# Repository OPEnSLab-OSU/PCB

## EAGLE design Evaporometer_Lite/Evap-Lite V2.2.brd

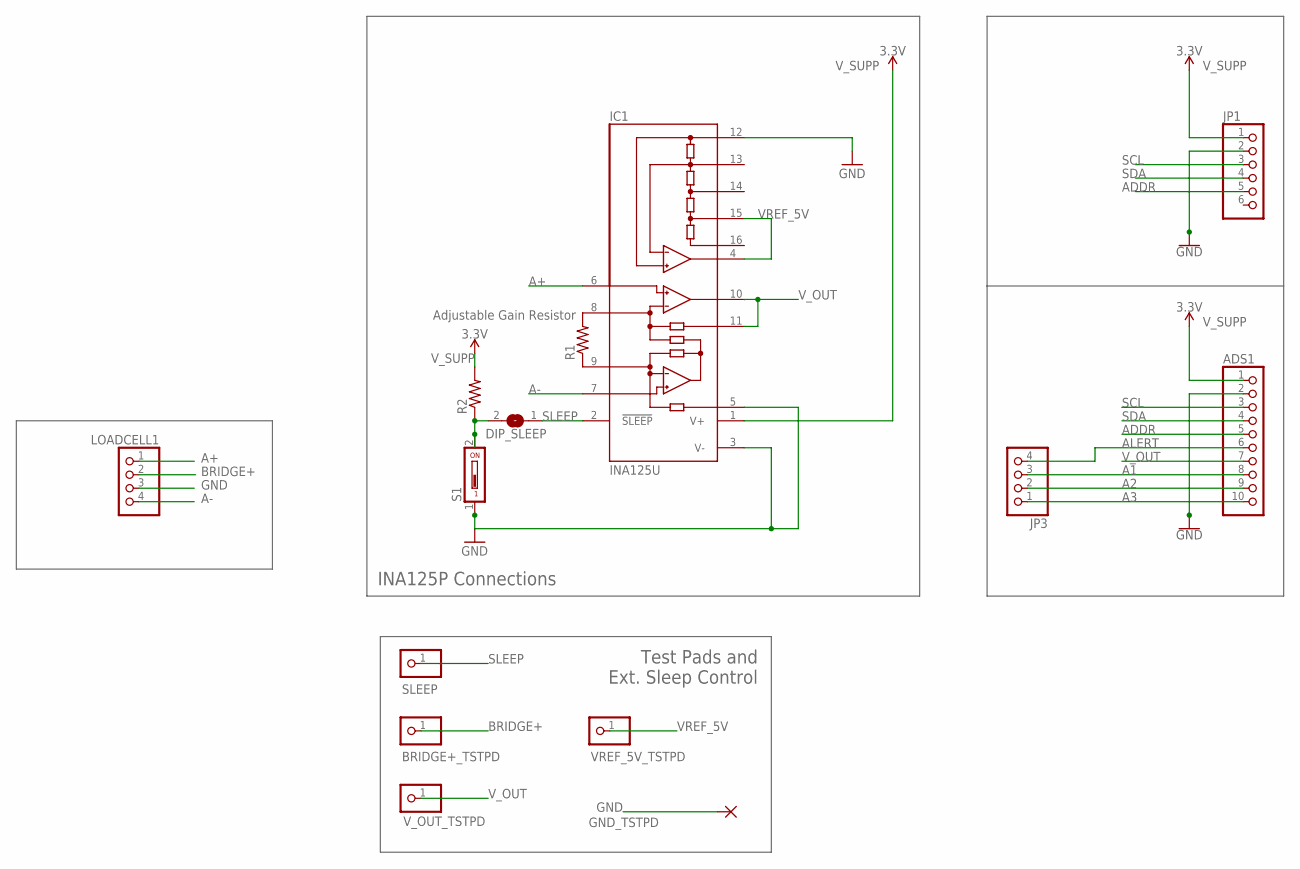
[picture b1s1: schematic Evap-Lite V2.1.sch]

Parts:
ADS1: PINHD-1X10; 1X10
BRIDGE+_TSTPD: PINHD-1X1; 1X01
DIP_SLEEP: SJ
GND_TSTPD: WIREPADSMD2,54-5,08; SMD2,54-5,08
IC1: INA125U; SO16-1
JP1: PINHD-1X6; 1X06
JP3: PINHD-1X4; 1X04
LOADCELL1: PINHD-1X4; 1X04
R1: R-US_R0603; R0603
R2: R-US_R1206; R1206
S1: DS01; DS-01
SLEEP: PINHD-1X1; 1X01
VREF_5V_TSTPD: PINHD-1X1; 1X01
V_OUT_TSTPD: PINHD-1X1; 1X01

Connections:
A1: ADS1.8, JP3.3
A2: ADS1.9, JP3.2
A3: ADS1.10, JP3.1
A+: IC1.6 (+IN), LOADCELL1.1
A-: IC1.7 (-IN), LOADCELL1.4
ADDR: ADS1.5, JP1.5
ALERT: ADS1.6, JP3.4
BRIDGE+: BRIDGE+_TSTPD.1, LOADCELL1.2
GND: ADS1.2, GND_TSTPD.1, IC1.3 (V-), IC1.5 (REF), IC1.12 (REFCOM), JP1.2, LOADCELL1.3, S1.1
unnamed: DIP_SLEEP.2, R2.1, S1.2
RG+: IC1.9 (RG), R1.1
RG-: IC1.8 (RG), R1.2
SCL: ADS1.3, JP1.3
SDA: ADS1.4, JP1.4
SLEEP: DIP_SLEEP.1, IC1.2 (!SLEEP), SLEEP.1
VREF_5V: IC1.4 (REFOUT), IC1.15 (REF5), VREF_5V_TSTPD.1
V_OUT: ADS1.7, IC1.10 (OUT), IC1.11 (SENSE), V_OUT_TSTPD.1
V_SUPP: ADS1.1, IC1.1 (V+), JP1.1, R2.2

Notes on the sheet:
Adjustable Gain Resistor
INA125P Connections
Test Pads and Ext. Sleep Control

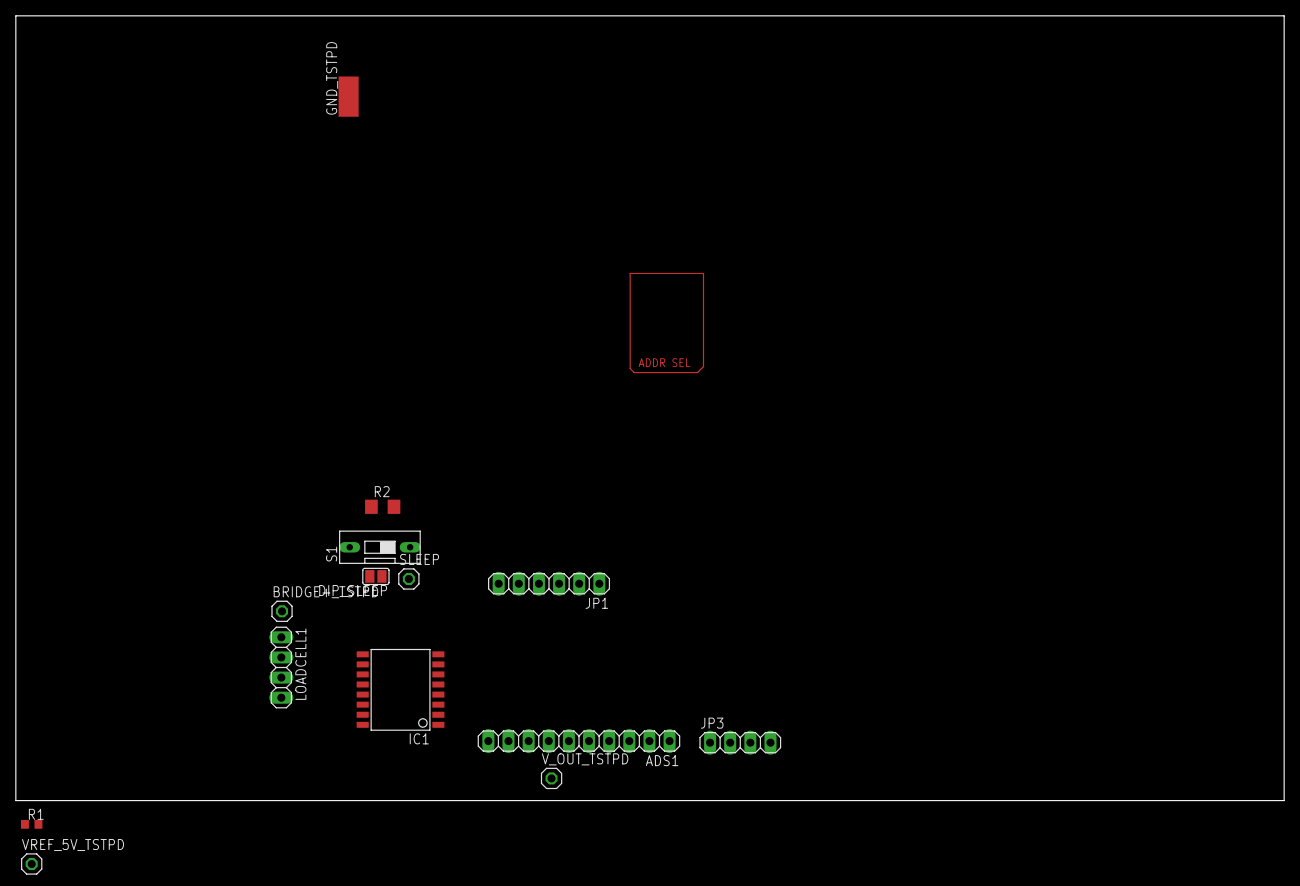
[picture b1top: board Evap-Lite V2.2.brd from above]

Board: 2 copper layers, 160.0 x 99.0 mm, 14 parts (0 on the bottom side), 18 nets.

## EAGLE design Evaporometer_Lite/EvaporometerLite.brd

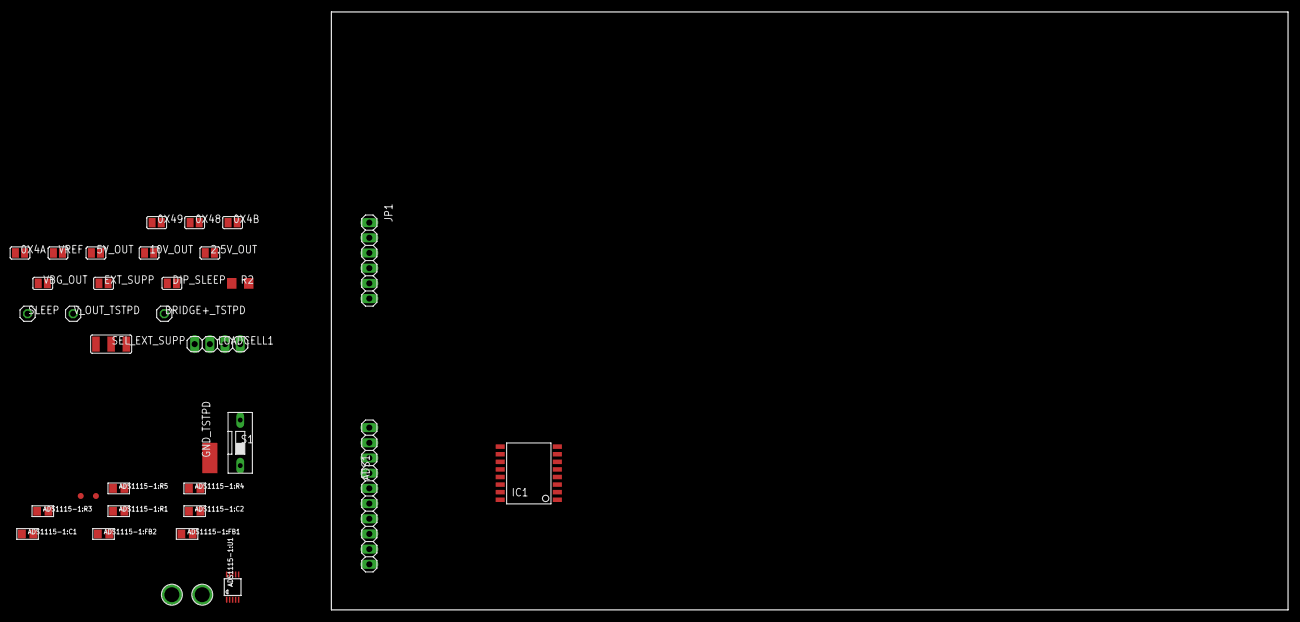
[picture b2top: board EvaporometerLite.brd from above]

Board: 2 copper layers, 160.0 x 100.0 mm, 35 parts (0 on the bottom side), 24 nets, no tracks yet.

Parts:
0X4A, 0X4B, 0X48, 0X49, 2.5V_OUT, 5V_OUT, 10V_OUT: SJ
ADS1: 1X10
ADS1115-1:C1, ADS1115-1:C2: 1µF; 0805
ADS1115-1:FB1, ADS1115-1:FB2: MMZ2012Y152B; 0805
ADS1115-1:FID1, ADS1115-1:FID2: FIDUCIAL""; FIDUCIAL_1MM
ADS1115-1:R1, ADS1115-1:R3, ADS1115-1:R4, ADS1115-1:R5: 10K; 0805
ADS1115-1:U1: ADS1115IDGST; MSOP10
ADS1115-1:U$13, ADS1115-1:U$14: MOUNTINGHOLE2.5; MOUNTINGHOLE_2.5_PLATED
BRIDGE+_TSTPD: 1X01
DIP_SLEEP: SJ
EXT_SUPP: SJ
GND_TSTPD: WIREPADSMD2,54-5,08; SMD2,54-5,08
IC1: INA125U; SO16-1
JP1: 1X06
LOADCELL1: 1X04
R2: R1206
S1: DS-01
SEL_EXT_SUPP: SJ_2W
SLEEP: 1X01
VBG_OUT: SJ
VREF: SJ
V_OUT_TSTPD: 1X01

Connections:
A1: ADS1.8, ADS1115-1:U1.5
A2: ADS1.9, ADS1115-1:U1.6
A3: ADS1.10, ADS1115-1:U1.7
A+: IC1.6, LOADCELL1.1
A-: IC1.7, LOADCELL1.4
ADDR: 0X4A.2, 0X4B.2, 0X48.2, 0X49.2, ADS1.5, ADS1115-1:R4.1, ADS1115-1:U1.1, JP1.5
ADS1115-1:GND: ADS1115-1:C1.1, ADS1115-1:FB2.2, ADS1115-1:R4.2, ADS1115-1:U1.3
ADS1115-1:VDD: ADS1115-1:C1.2, ADS1115-1:FB1.2, ADS1115-1:R1.1, ADS1115-1:R3.1, ADS1115-1:R5.1, ADS1115-1:U1.8
ALERT: ADS1.6, ADS1115-1:R5.2, ADS1115-1:U1.2
BRIDGE+: BRIDGE+_TSTPD.1, EXT_SUPP.1, LOADCELL1.2, VREF.1
GND: 0X48.1, ADS1.2, ADS1115-1:C2.2, ADS1115-1:FB2.1, GND_TSTPD.1, IC1.3, IC1.5, IC1.12, JP1.2, LOADCELL1.3, S1.1
unnamed: JP1.6, SEL_EXT_SUPP.3
unnamed: DIP_SLEEP.2, R2.1, S1.2
SCL: 0X4B.1, ADS1.3, ADS1115-1:R1.2, ADS1115-1:U1.10, JP1.3
SDA: 0X4A.1, ADS1.4, ADS1115-1:R3.2, ADS1115-1:U1.9, JP1.4
SLEEP: DIP_SLEEP.1, IC1.2, SLEEP.1
VREF_2.5V: 2.5V_OUT.2, IC1.14
VREF_5V: 5V_OUT.2, IC1.15
VREF_10V: 10V_OUT.2, IC1.16
VREF_BG: IC1.13, VBG_OUT.2
VREF_EXT: EXT_SUPP.2, SEL_EXT_SUPP.2
VREF_OUT: 2.5V_OUT.1, 5V_OUT.1, 10V_OUT.1, IC1.4, VBG_OUT.1, VREF.2
V_OUT: ADS1.7, ADS1115-1:U1.4, IC1.10, IC1.11, V_OUT_TSTPD.1
V_SUPP: 0X49.1, ADS1.1, ADS1115-1:C2.1, ADS1115-1:FB1.1, IC1.1, JP1.1, R2.2, SEL_EXT_SUPP.1

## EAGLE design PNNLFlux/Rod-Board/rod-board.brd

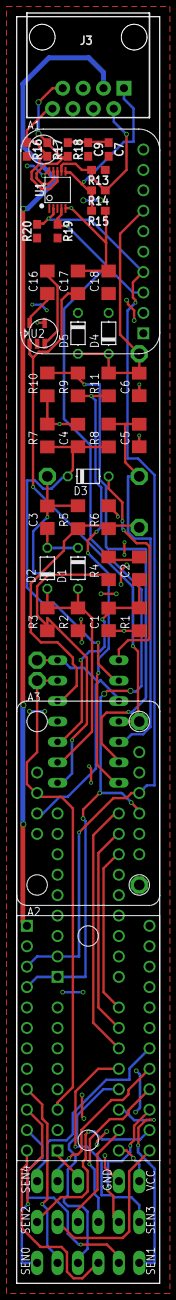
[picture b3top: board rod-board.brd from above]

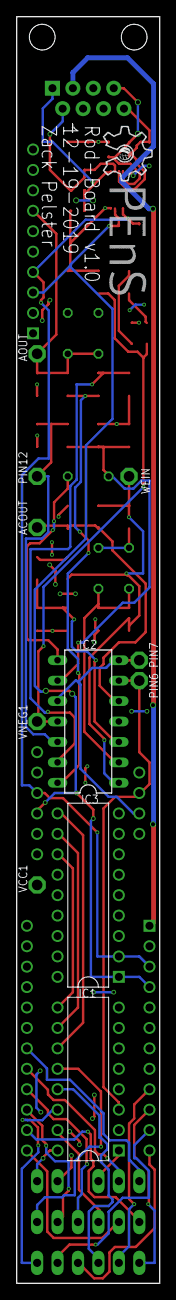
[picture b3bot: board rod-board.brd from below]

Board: 2 copper layers, 17.8 x 157.5 mm, 59 parts (12 on the bottom side), 44 nets.

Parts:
A1: ADS1115
A2: TCA9548A
A3: DS3502
ACOUT: PTR1PAD1-13; P1-13
AOUT: PTR1PAD1-13; P1-13
C1, C2, C3: 100nF; C1206
C4, C5, C6, C16, C17, C18: 1uF; C1206
C7: 0.1uF; 0603
C9: 1.0uF; 0603
D1, D2, D3, D4, D5: 1N4001; D-5
IC1: CD4051BE
IC2: TL074P; DIL14
IC3: MCP23008
J3: RJ45; RJ45-8
JP1: SENSOR0; 1X03
JP2: SENSOR1; 1X03
JP3: SENSOR2; 1X03
JP4: SENSOR3; 1X03
JP5: SENSOR4; 1X03
JP6: POWER; 1X02
PIN6, PIN7, PIN12: PTR1PAD1-13; P1-13
R1, R4, R6: 1K; R1206
R2, R7, R9: 10K; R1206
R3: 22K; R1206
R5: 2K; R1206
R8, R11: 4.7K; R1206
R10: 5K; R1206
R13, R15, R16, R18: 390; 0603
R14, R17: 100; 0603
R19, R20: 4.7k; 0603
U1: PCA9615; TSSOP10
U2: TPS60400DBVR; SOT95P280X145-5N
U$1: OPENS-LOGO
VCC1: PTR1PAD1-13; P1-13
VNEG1: PTR1PAD1-13; P1-13
WEIN: PTR1PAD1-13; P1-13

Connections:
3V_I2C: A2.VIN, J3.3
A: IC1.A, IC3.GP0
AIN: A3.RH, IC1.COM, IC2.6, PIN6.TP
AOUT: A1.A0, AOUT.TP, C6.2, D4.C, D5.A, R11.2
B: IC1.B, IC3.GP1
C: IC1.C, IC3.GP2
DSCL+: J3.2, R13.1, R14.2, U1.7
DSCL-: J3.1, R14.1, R15.2, U1.6
DSDA+: J3.8, R16.1, R17.2, U1.8
DSDA-: J3.7, R17.1, R18.2, U1.9
EC0: IC1.0, JP1.3
EC1: IC1.1, JP2.3
EC2: IC1.2, JP3.3
EC3: IC1.3, JP4.3
EC4: IC1.4, JP5.3
GND: A1.GND, A2.GND, A3.GND, A3.RL, C1.2, C4.1, C5.1, C6.1, C7.2, C9.2, C17.1, C18.1, D4.A, IC1.VEE, IC3.VSS, J3.5, JP6.1, R1.1, R2.2, R6.1, R7.1, R10.2, R15.1, R18.1, U1.5, U2.4
unnamed: C1.1, C2.1, IC2.3, R1.2
unnamed: C2.2, R4.2
unnamed: C3.2, IC2.1, R3.1, R4.1, R5.2, WEIN.TP
unnamed: D1.A, D2.C, IC2.2, R2.1, R3.2
unnamed: ACOUT.TP, IC2.5, R5.1, R6.2
unnamed: C3.1, D1.C, D2.A
unnamed: C4.2, D3.C, IC2.9, R7.2, R8.2
unnamed: D3.A, IC2.8
unnamed: C5.2, IC2.12, PIN12.TP, R8.1
unnamed: IC2.13, R9.2, R10.1
unnamed: IC2.14, R9.1, R11.1
unnamed: C16.2, U2.5
unnamed: C16.1, U2.3
POT: A3.RW, IC2.7, IC2.10, PIN7.TP
SC0: A2.SC0, JP1.1
SC1: A2.SC1, JP2.1
SC2: A2.SC2, JP3.1
SC3: A2.SC3, JP4.1
SC4: A2.SC4, JP5.1
SCL: A1.SCL, A2.SCL, A3.SCL, IC3.SCL, R19.1, U1.4
SD0: A2.SD0, JP1.2
SD1: A2.SD1, JP2.2
SD2: A2.SD2, JP3.2
SD3: A2.SD3, JP4.2
SD4: A2.SD4, JP5.2
SDA: A1.SDA, A2.SDA, A3.SDA, IC3.SDA, R20.1, U1.2
VCC: A1.VDD, A3.VCC, C7.1, C9.1, C18.2, D5.C, IC1.VDD, IC2.4, IC3.VDD, J3.4, JP6.2, R13.2, R16.2, R19.2, R20.2, U1.1, U1.10, U2.2, VCC1.TP
VNEG: C17.2, IC2.11, U2.1, VNEG1.TP

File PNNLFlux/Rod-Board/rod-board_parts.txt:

Partlist

Exported from rod-board.brd at 12/20/19 8:15 AM

EAGLE Version 9.5.1 Copyright (c) 1988-2019 Autodesk, Inc.

Assembly variant: 

Part     Value          Package          Library             Position (inch)       Orientation

A1       ADS1115        ADS1115          PNNL_Probe          (0.7 3.3)             R90
A2       TCA9548A       TCA9548A         PNNL_Probe          (0 4.45)              R0
A3       DS3502         DS3502           PNNL_Probe          (0.7 2.25)            R90
ACOUT    PTR1PAD1-13    P1-13            testpad             (0.6 1.2)             R0
AOUT     PTR1PAD1-13    P1-13            testpad             (0.6 2.1)             R0
C1       100nF          C1206            rcl                 (0.45 0.75)           R270
C2       100nF          C1206            rcl                 (0.6 1)               R90
C3       100nF          C1206            rcl                 (0.15 1.25)           R90
C4       1uF            C1206            rcl                 (0.3 1.65)            R270
C5       1uF            C1206            rcl                 (0.6 1.65)            R90
C6       1uF            C1206            rcl                 (0.6 1.9)             R90
C7       0.1uF          0603             SparkFun-Capacitors (0.25 5.6)            R270
C9       1.0uF          0603             SparkFun-Capacitors (0.45 5.6)            R270
C16      1uF            C1206            rcl                 (0.15 2.4)            R270
C17      1uF            C1206            rcl                 (0.3 2.4)             R270
C18      1uF            C1206            rcl                 (0.45 2.4)            R270
D1       1N4001         D-5              diode               (0.3 1)               R270
D2       1N4001         D-5              diode               (0.15 1)              R90
D3       1N4001         D-5              diode               (0.35 1.45)           R0
D4       1N4001         D-5              diode               (0.45 2.15)           R90
D5       1N4001         D-5              diode               (0.3 2.15)            R270
IC1      CD4051BE       CD4051BE         PNNL_Probe          (0.15 3.45)           MR90
IC2      TL074P         DIL14            linear              (0.35 3)              MR90
IC3      MCP23008       MCP23008         PNNL_Probe          (0.1 4.25)            MR90
J3       RJ45           RJ45-8           SparkFun-Connectors (0.35 6.1)            R180
JP1                     1X03             pinhead             (0.2 0.1)             R0
JP2                     1X03             pinhead             (0.5 0.1)             R0
JP3                     1X03             pinhead             (0.2 0.3)             R0
JP4                     1X03             pinhead             (0.5 0.3)             R0
JP5                     1X03             pinhead             (0.2 0.5)             R0
JP6                     1X02             pinhead             (0.55 0.5)            R0
PIN6     PTR1PAD1-13    P1-13            testpad             (0.6 3.2)             MR0
PIN7     PTR1PAD1-13    P1-13            testpad             (0.1 3.1)             MR0
PIN12    PTR1PAD1-13    P1-13            testpad             (0.6 1.45)            R0
R1       1K             R1206            rcl                 (0.6 0.75)            R90
R2       10K            R1206            rcl                 (0.3 0.75)            R270
R3       22K            R1206            rcl                 (0.15 0.75)           R90
R4       1K             R1206            rcl                 (0.45 1)              R90
R5       2K             R1206            rcl                 (0.3 1.25)            R90
R6       1K             R1206            rcl                 (0.45 1.25)           R270
R7       10K            R1206            rcl                 (0.15 1.65)           R270
R8       4.7K           R1206            rcl                 (0.45 1.65)           R270
R9       10K            R1206            rcl                 (0.3 1.9)             R90
R10      5K             R1206            rcl                 (0.15 1.9)            R270
R11      4.7K           R1206            rcl                 (0.45 1.9)            R90
R13      390            0603             SparkFun-Resistors  (0.55 5.6)            R90
R14      100            0603             SparkFun-Resistors  (0.55 5.45)           R90
R15      390            0603             SparkFun-Resistors  (0.55 5.3)            R90
R16      390            0603             SparkFun-Resistors  (0.15 5.6)            R90
R17      100            0603             SparkFun-Resistors  (0.15 5.45)           R90
R18      390            0603             SparkFun-Resistors  (0.15 5.3)            R90
R19      4.7k           0603             SparkFun-Resistors  (0.25 5.2)            R0
R20      4.7k           0603             SparkFun-Resistors  (0.45 5.2)            R180
U1       PCA9615        TSSOP10          SparkFun-IC-Comms   (0.35 5.4)            R0
U2       TPS60400DBVR   SOT95P280X145-5N TPS60400DBVR        (0.1 2.15)            R90
VCC1     PTR1PAD1-13    P1-13            testpad             (0.6 2.35)            MR270
VNEG1    PTR1PAD1-13    P1-13            testpad             (0.1 3)               MR0
WEIN     PTR1PAD1-13    P1-13            testpad             (0.15 1.45)           R0

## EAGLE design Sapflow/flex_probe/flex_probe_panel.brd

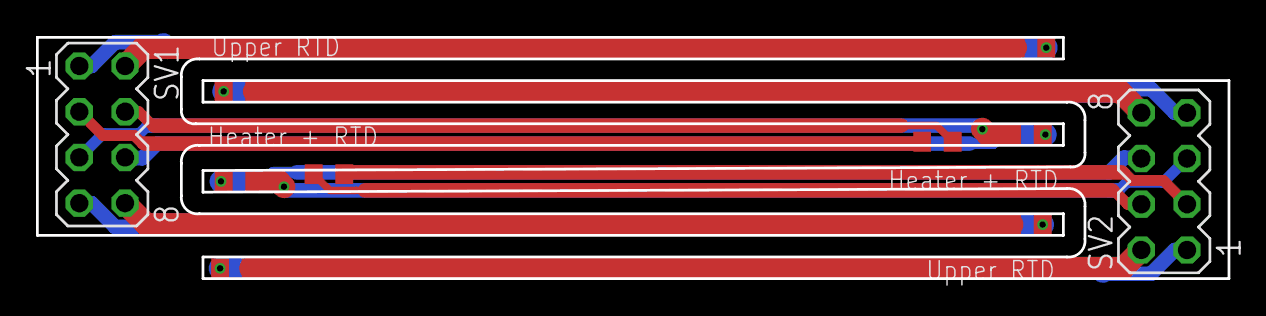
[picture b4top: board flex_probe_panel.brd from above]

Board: 2 copper layers, 66.2 x 13.4 mm, 10 parts (0 on the bottom side), 16 nets.

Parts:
R1, R2, R4, R5, R6, R8: RTD; R0603
R3, R7: 100; R0603
SV1, SV2: MA04-2

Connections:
unnamed: R1.2, SV1.2
unnamed: R1.1, SV1.1
unnamed: R2.2, SV1.4
unnamed: R2.1, SV1.3
unnamed: R6.2, SV2.4
unnamed: R6.1, SV2.3
unnamed: R4.1, SV1.7
unnamed: R3.2, SV1.6
unnamed: R3.1, SV1.5
unnamed: R8.1, SV2.7
unnamed: R4.2, SV1.8
unnamed: R7.2, SV2.6
unnamed: R7.1, SV2.5
unnamed: R5.2, SV2.2
unnamed: R5.1, SV2.1
unnamed: R8.2, SV2.8

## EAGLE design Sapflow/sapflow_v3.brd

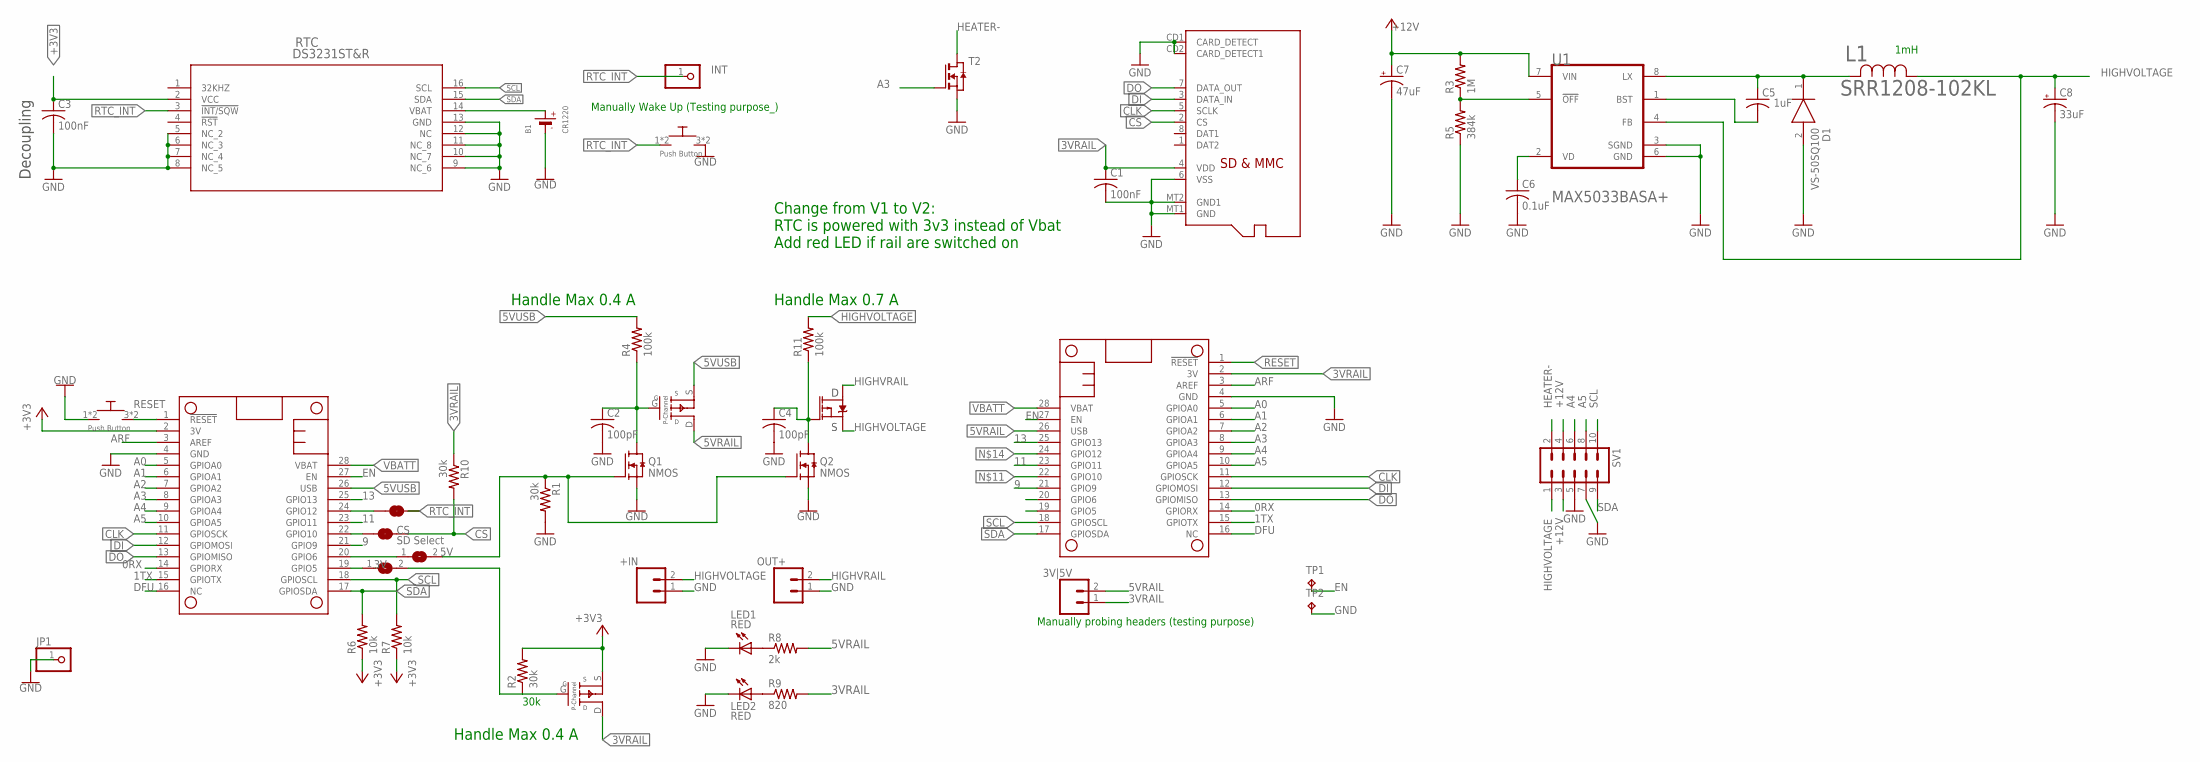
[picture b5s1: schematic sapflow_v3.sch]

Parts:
3V, 5V: SJ
3V|5V: CONN_021X02_NO_SILK; 1X02_NO_SILK
+IN: HIGHV-IN; 1X02_NO_SILK
B1: CR1220
C1, C3: 100nF; C1206
C2, C4: 100pF; C0805
C5: 1uF; C0603
C6: 0.1uF; C0603
C7: 47uF; D/7343-31R
C8: 33uF; D/7343-31R
CS: SD Select; SMT-JUMPER_2_NC_TRACE_SILK
D1: VS-50SQ100; DIOAD1405W86L465D235
INT: PINHD-1X1CB; 1X01-CLEANBIG
JP1: PINHD-1X1CB; 1X01-CLEANBIG
L1: SRR1208-102KL; IND_BOURNS_SRR1208
LED1, LED2: RED; CHIPLED_0805
MICROSD: MICROSD
MS1, MS2: FEATHERWING
OUT+: HIGHV-OUT; 1X02_NO_SILK
PMOS1, PMOS2: SSM3J3228R; SOT-23-3
PMOS3: P-MOSFET; SOT23-6
Q1, Q2: NMOS; SOT23-S
R1, R2, R10: 30k; RES_1206
R3: 1M; R0603
R4, R11: 100k; RES_1206
R5: 384k; R0603
R6, R7: 10k; RES_1206
R8: 2k; RES_1206
R9: 820; RES_1206
RTC: DS3231ST&R; 21-0042B_16
RTC_INT: JUMPER-SMT_2_NC_TRACE_SILK; SMT-JUMPER_2_NC_TRACE_SILK
SV1: MA05-2
T2: NMOSSOT223; SOT223
TP1, TP2: TPTP16R; TP16R
U1: MAXIM_MAX5033BASA+MAXIM_MAX5033BASA+_0_1; MAXIM_MAX5033BASA+_1
U$1, U$2: PUSH_BUTTON; PUSHBUTTON_SMD

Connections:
0RX: MS1.14 (GPIORX), MS2.14 (GPIORX)
1TX: MS1.15 (GPIOTX), MS2.15 (GPIOTX)
3VRAIL: 3V|5V.1, C1.1, MICROSD.4 (VDD), MS1.2 (3V), PMOS2.D, R9.2, R10.1
5VRAIL: 3V|5V.2, MS1.26 (USB), PMOS1.D, R8.2
5VUSB: MS2.26 (USB), PMOS1.S, R4.2
9: MS1.21 (GPIO9), MS2.21 (GPIO9)
11: MS1.23 (GPIO11), MS2.23 (GPIO11)
13: MS1.25 (GPIO13), MS2.25 (GPIO13)
+3V3: C3.1, MS2.2 (3V), PMOS2.S, R2.2, R6.1, R7.1, RTC.2 (VCC)
+12V: C7.+, R3.2, SV1.3, SV1.4, U1.7 (VIN)
A0: MS1.5 (GPIOA0), MS2.5 (GPIOA0)
A1: MS1.6 (GPIOA1), MS2.6 (GPIOA1)
A2: MS1.7 (GPIOA2), MS2.7 (GPIOA2)
A3: MS1.8 (GPIOA3), MS2.8 (GPIOA3), T2.1 (G)
A4: MS1.9 (GPIOA4), MS2.9 (GPIOA4), SV1.6
A5: MS1.10 (GPIOA5), MS2.10 (GPIOA5), SV1.8
ARF: MS1.3 (AREF), MS2.3 (AREF)
CLK: MICROSD.5 (SCLK), MS1.11 (GPIOSCK), MS2.11 (GPIOSCK)
CS: CS.2, MICROSD.2 (CS), R10.2
DFU: MS1.16 (NC), MS2.16 (NC)
DI: MICROSD.3 (DATA_IN), MS1.12 (GPIOMOSI), MS2.12 (GPIOMOSI)
DO: MICROSD.7 (DATA_OUT), MS1.13 (GPIOMISO), MS2.13 (GPIOMISO)
EN: MS1.27 (EN), MS2.27 (EN), TP1.TP
GND: +IN.1, B1.-, C1.2, C2.2, C3.2, C4.2, C6.2, C7.-, C8.-, D1.2 (A), JP1.1, LED1.C, LED2.C, MICROSD.6 (VSS), MICROSD.CD1 (CARD_DETECT), MICROSD.CD2 (CARD_DETECT1), MICROSD.MT1 (GND), MICROSD.MT2 (GND1), MS1.4 (GND), MS2.4 (GND), OUT+.1, Q1.2 (S), Q2.2 (S), R1.2, R5.1, RTC.5 (NC_2), RTC.6 (NC_3), RTC.7 (NC_4), RTC.8 (NC_5), RTC.9 (NC_6), RTC.10 (NC_7), RTC.11 (NC_8), RTC.12 (NC), RTC.13 (GND), SV1.5, SV1.7, T2.3 (S), TP2.TP, U1.3 (SGND), U1.6 (GND), U$1.1, U$1.2, U$2.3, U$2.4
HEATER-: SV1.2, T2.2 (D), T2.4 (D)
HIGHVOLTAGE: +IN.2, C8.+, L1.1, PMOS3.4 (S), R11.2, SV1.1, U1.4 (FB)
HIGHVRAIL: OUT+.2, PMOS3.1 (D), PMOS3.2 (D), PMOS3.5 (D), PMOS3.6 (D)
unnamed: 5V.1, MS2.20 (GPIO6)
unnamed: B1.+$1 (+), RTC.14 (VBAT)
unnamed: 3V.1, MS2.19 (GPIO5)
unnamed: 5V.2, Q1.1 (G), Q2.1 (G), R1.1
unnamed: 3V.2, PMOS2.G, R2.1
unnamed: C6.1, U1.2 (VD)
unnamed: R3.1, R5.2, U1.5 (!OFF!)
unnamed: C2.1, PMOS1.G, Q1.3 (D), R4.1
unnamed: CS.1, MS1.22 (GPIO10), MS2.22 (GPIO10)
unnamed: LED1.A, R8.1
unnamed: LED2.A, R9.1
unnamed: MS1.24 (GPIO12), MS2.24 (GPIO12), RTC_INT.1
unnamed: C4.1, PMOS3.3 (G), Q2.3 (D), R11.1
unnamed: C5.2, U1.1 (BST)
unnamed: C5.1, D1.1 (K), L1.2, U1.8 (LX)
RESET: MS1.1 (!RESET), MS2.1 (!RESET), U$1.3, U$1.4
RTC_INT: INT.1, RTC.3 (!INT/SQW), RTC_INT.2, U$2.1, U$2.2
SCL: MS1.18 (GPIOSCL), MS2.18 (GPIOSCL), R7.2, RTC.16 (SCL), SV1.10
SDA: MS1.17 (GPIOSDA), MS2.17 (GPIOSDA), R6.2, RTC.15 (SDA), SV1.9
VBATT: MS1.28 (VBAT), MS2.28 (VBAT)

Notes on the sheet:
Decoupling
Manually Wake Up (Testing purpose_)
Manually probing headers (testing purpose)
30k
Change from V1 to V2: RTC is powered with 3v3 instead of Vbat Add red LED if rail are switched on
Handle Max 0.7 A
Handle Max 0.4 A
1mH

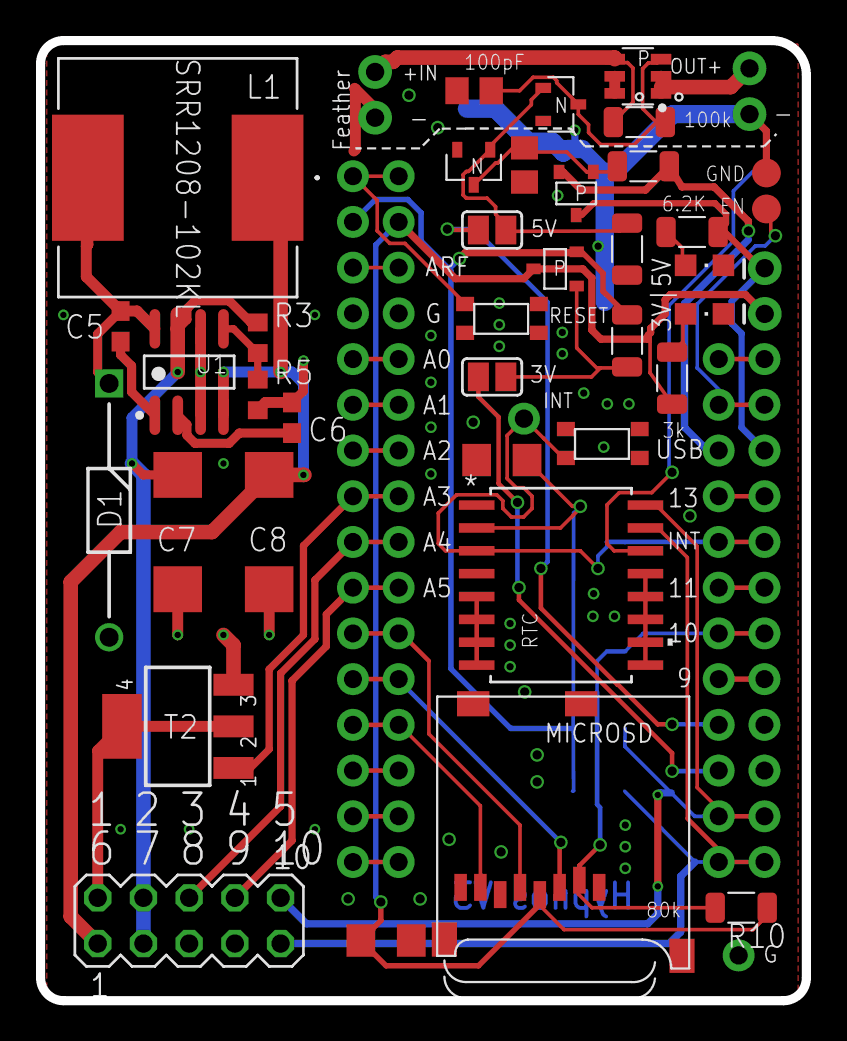
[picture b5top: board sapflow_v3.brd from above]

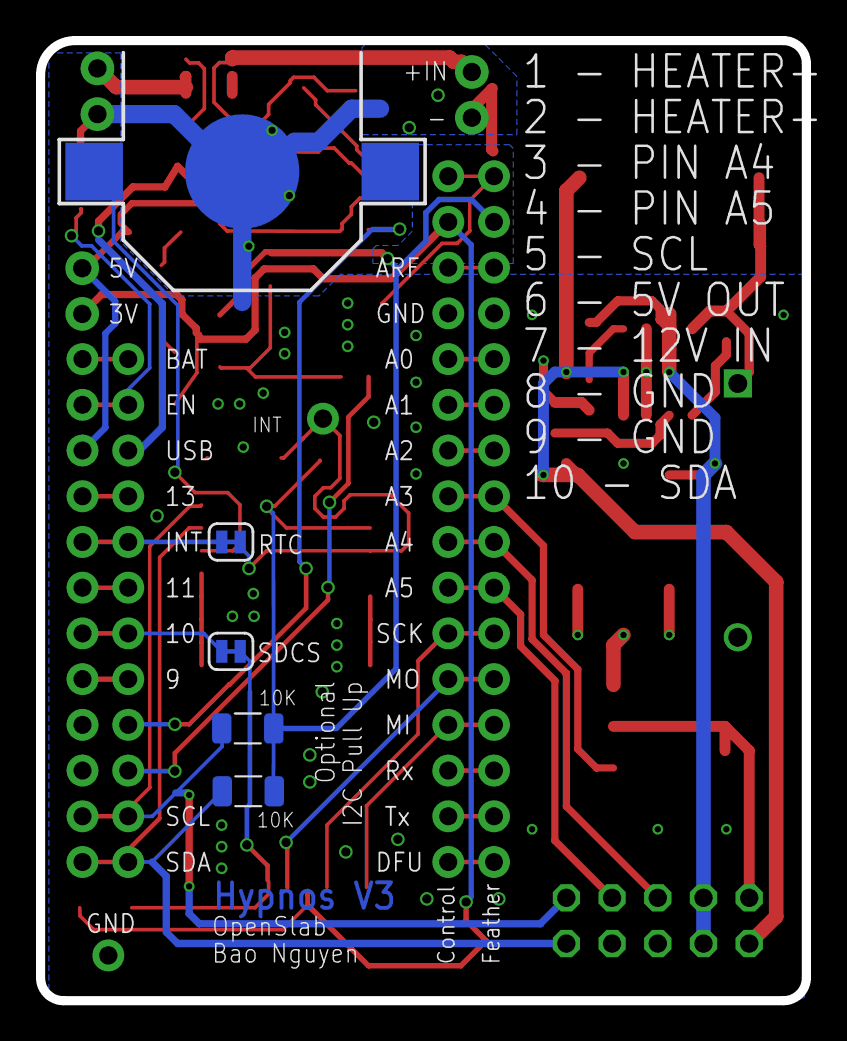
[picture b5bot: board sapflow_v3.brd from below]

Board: 2 copper layers, 42.5 x 53.3 mm, 49 parts (6 on the bottom side), 47 nets.

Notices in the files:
parts and their libraries:
SparkFun-PowerSymbols: Licensing: Creative Commons ShareAlike 4.0 International - https://creativecommons.org/licenses/by-sa/4.0
microbuilder: This work is placed in the public domain, and may be freely used for commercial and non-commercial work with the following conditions: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
